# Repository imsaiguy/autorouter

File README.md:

# Visible Autorouter for KiCad

A multi-pass PCB autorouter that runs **inside KiCad** (toolbar button) or from the
command line, routes **all nets or just the ones you select**, and **shows its
thinking** while it works.

*Pass 1: every net takes its own shortest path and nets pile on top of each other
(yellow squares). Each later pass raises the price of contested copper. The
orange heat is the congestion "memory" the router has learned. Nets that have
alternatives move away; the curve on the right shows the overuse falling to
zero.*

## Get it

```bash
git clone https://github.com/imsaiguy/autorouter.git
```

or use **Code ▸ Download ZIP** on https://github.com/imsaiguy/autorouter. The
plugin is the `kicad_autorouter` folder; installation is described below.

### Install or update on Windows in one go (KiCad 10)

Save your work, then paste this into PowerShell. It closes KiCad, downloads the
latest version and installs it (the same block installs the first time and
updates afterwards):

```powershell
Get-Process python*, pythonw* -ErrorAction SilentlyContinue | Where-Object { $_.Path -like "*KiCad*" } | Stop-Process -Force
Get-Process kicad*, pcbnew*, eeschema* -ErrorAction SilentlyContinue | Stop-Process
Remove-Item -Recurse -Force "$env:TEMP\autorouter" -ErrorAction SilentlyContinue
Invoke-WebRequest https://github.com/imsaiguy/autorouter/archive/refs/heads/main.zip -OutFile "$env:TEMP\autorouter.zip"
Expand-Archive "$env:TEMP\autorouter.zip" "$env:TEMP\autorouter" -Force
"y" | & "C:\Program Files\KiCad\10.0\bin\python.exe" -u "$env:TEMP\autorouter\autorouter-main\kicad_autorouter\install_plugin.py"
```

Then start KiCad and open a board. The router's log should say
**"Search core: compiled (fast)"**.

## What it does

* **Three scopes:**
  * **Unrouted only** (the default): finishes just the missing connections,
    i.e. the ratsnest. **Existing tracks and vias are never moved or
    removed.** Partly routed nets get only their missing links, and new
    copper joins onto what's there.
  * **Selected:** the nets of the selected footprints, pads or tracks.
  * **All nets.**

  For *Selected* and *All* you can tick **Remove existing tracks** to re-route
  those nets from scratch. Otherwise existing copper is kept: connected pieces
  count as one terminal, and other nets' tracks are obstacles.
* **Global then detailed routing.** A coarse stage first plans each net's way
  through 2.7 mm regions, with PathFinder on region boundaries that have a
  capacity. The detailed grid search then stays inside that corridor, which
  widens if a net keeps conflicting and falls back to the full search if it is
  too tight. This is the same idea as tscircuit's capacity-mesh router. On the
  dense test board it is about 1.7× faster (60 s → 35 s) for about 2% more track
  length. Turn it off with `--no-global`.
* **Clean, 45° routing.** Every bend is 45°: no 90° corners, no hairpins.
  Straightening is always the last step (no option to turn it off): zig-zags,
  bumps, jogs and awkward joins become straight runs wherever the space is
  free, without cutting pours. The test suite checks that
  results have no corners sharper than 45° and no dead-end stubs.
* **Loose copper.** Track pieces that touch no pad (e.g. an unfinished trace)
  are never routed *to*, because that only grows dead-end stubs. They are
  reported, and **"Delete loose track pieces"** removes them in the same undo
  step.
* **Clear progress.** A progress bar with an estimated time remaining, a bar
  for the current pass, and live detail (pass, net *n* of *m*, conflicts left,
  elapsed time), with big **Route / Stop / Close** buttons. The estimate is
  learned from how fast conflicts are falling, and the bar never runs
  backwards.
* **Sees your existing work.** When it loads the design it shows existing
  tracks and vias (muted, so new routes stand out) and a summary such as
  *"8 routed · 1 partly routed · 2 unrouted"*. If a net can't be finished
  around fixed copper, it says which net and how to free it.
* **Multiple passes.** It uses the negotiated-congestion "PathFinder" algorithm
  with A* search per connection, which is the standard method for FPGA routing.
* **Visible thinking.** You can watch the A* wavefront, tentative tracks,
  overused cells, the learned congestion heatmap, and a convergence curve,
  either in the plugin's browser view, in a matplotlib window, or as a GIF.
* **Pours only count where they reach.** A pad counts as connected by a pour
  only if it lies inside that zone's outline. Every other pad of a pour net
  (GND, +5…) is routed into the pour, tree-style, so nearby pads share a track.
  The option **Route pour nets with tracks too** routes them like any other net.
* **Pours are part of the negotiation.** GND/power nets with a copper zone are
  left to the pour. SMD pads that are not on the pour layer get a short stub
  plus a via down to it. After each pass the router estimates the pour,
  detects pads or vias stranded on islands, and pushes the tracks that cut
  them off elsewhere.
* **Fast.** The A* search runs in a small compiled C library (`native/`,
  Linux x86-64 and Windows x64 shipped; elsewhere it falls back to the same
  search in Python, about 3–4× slower). Pass 1 runs on several CPU cores at once
  (one worker process per core, biggest nets first). A 120-net board with
  0.5 mm-pitch parts routes in about 30–60 s.
* **Net classes.** Each net keeps its class's track width and clearance (read
  from the `.kicad_pro`, or from KiCad itself in the plugins).
* **Ground planes done properly.** When a pour net (GND…) has a pour on
  another layer, every SMD pad gets its own short via down to it (or shares a
  neighbour's), instead of tracks wandering between pads. Signals have
  priority: a via that would block another net gives way. Zone outlines, zone
  priority and zone clearance are taken into account.
* **Solid planes.** On boards with more than two layers, an inner layer covered by
  a pour (GND or power plane) stays solid: other nets only pass through it with
  vias. Tick **Allow tracks on plane layers** (`--tracks-on-planes`) to route
  signals there too. Ground and power have priority: they are never dropped to
  make room for signals.
* **Fine-pitch escapes.** Pads too close together for the grid get a short
  off-grid stub (down to the minimum track width) to the nearest usable grid
  point.
* **A second chance for dropped nets.** If the negotiation has to drop a few
  nets, a rescue pass tries each again on the finished board, and then
  re-routes it together with the nets it was fighting, in every order (up to
  3 s per net).
* **Says why.** Nets that could not be finished are listed with the reason:
  walled in (by which pads or tracks), or "no room left - it was fighting X
  and Y for the same space".
* **Stop when you like.** Stop offers two choices: **Discard** (nothing is
  written) or **Keep**, which straightens what was routed, exactly like a
  finished run.
* **Straighten a board from the command line.** `--straighten-only` runs the
  same clean-up on the copper already in a `.kicad_pcb` file, without routing
  anything (off-grid pieces such as hand-drawn tracks stay as they are).
* **Checked with KiCad's own DRC.** On the demo board the result has
  **0 clearance, short, edge or hole violations and 0 unconnected items**.
  The test suite runs that check.

## How it thinks

The board becomes a grid whose pitch is `track width + clearance`. Tracks run
along cell centres, so *one cell = one net* **is** the clearance rule. Two extra
rules keep that true everywhere else:

* a 45° step must clear fixed copper at its middle point (checked on a second
  map, offset half a cell), and it books the two side cells it squeezes past:
  another net's track there is a conflict, another 45° step's side cell is
  not (two parallel diagonals one cell apart are 1.41 pitch apart);
* a via claims every cell within `via radius + clearance + track width/2`, on
  every layer;
* a net in a wider net class (say a 24 mil "power" class) claims a square of
  `r` cells round its centre-line, the smallest `r` with
  `(r + 1) · pitch ≥ W/2 + w/2 + C` (W, C: the class's width and clearance;
  w: the Default width). It keeps that width all the way; only in the last
  cell or two before one of its own pads, where the neighbouring pads leave
  no room, may it narrow to the Default width.
* a new branch may leave or join an earlier track of its net only at 90° or
  wider (a T, never a sharp Y), and the clean-up pass keeps it that way.

Pads, existing tracks and the board edge give each cell an owner: free, "only
net *n*" (inside *n*'s clearance halo), or blocked.

Each pass then does this:

```
global plan: PathFinder on a coarse grid of regions -> one corridor per net
for each net that is in conflict:              (all nets in pass 1)
    rip up its old route
    grow a tree from one pad; repeatedly A* to the nearest unconnected pad
        cost of a cell = (1 + history) × (1 + present_factor × other_nets_in_cell)
        × direction factor (F.Cu prefers horizontal, B.Cu vertical) + bend + via costs
        the search state includes the arrival direction, so only 0° / 45° turns are allowed

after the pass:
    overused cell  = used by 2+ nets
    history       += history_factor × overuse        (remembers chronic hot spots)
    present_factor ×= 1.6                             (contention gets pricier every pass)
    pour check: a pour pad/via cut off onto an island → its walls get pricier too
stop when nothing is overused
then: straighten every route (zig-zag -> straight / straight+45°) using only free cells
```

This works like a market. Copper is a shared resource and its price rises with
demand. Nets with cheap alternatives leave the contested cells. Nets with no
alternative stay, because everyone else has learned to avoid that spot. The
present-cost factor only ever rises, so it also resembles annealing: the
system gradually "freezes" into a legal solution. If it hasn't converged after
`max_passes`, the most-conflicted nets are dropped and reported, so the output
is always DRC-legal.

## Install in KiCad

**KiCad 10 only.** The plugin uses KiCad's IPC API (the classic `pcbnew`
Python plugin interface is being retired by KiCad, and the old classic version
of this plugin has been removed; the installer deletes it if it finds it). Only
a tiny launcher button still uses the classic interface (see *Toolbar button*).

### KiCad 10

**Easiest: use the installer.** Close KiCad, then run it with the Python that
ships with KiCad:

```powershell
# Windows (PowerShell or cmd), from the folder you cloned / unzipped
& "C:\Program Files\KiCad\10.0\bin\python.exe" kicad_autorouter\install_plugin.py
```
```bash
# macOS / Linux
python3 kicad_autorouter/install_plugin.py
```

It does four things:

* copies the plugin to the folder KiCad 10 really loads from. It asks Windows
  for your Documents folder, so OneDrive-redirected Documents work.
* offers to remove stray copies from earlier attempts.
* turns on **Enable KiCad API** (it's off by default).
* checks the result.

Then start KiCad, open a board, and give it a minute the first time.

**Or by hand:**

1. **Turn the KiCad API on.** It is **off by default**. Go to
   **Preferences ▸ Preferences ▸ Plugins** and tick the option that enables
   the KiCad API.
2. **Copy the `kicad_autorouter` folder** (the whole folder, not its contents)
   into KiCad's **`plugins`** folder. Create the folder if it doesn't exist.

   | OS | folder |
   |---|---|
   | Windows | `Documents\KiCad\10.0\plugins\` |
   | macOS | `~/Documents/KiCad/10.0/plugins/` |
   | Linux | `~/.local/share/kicad/10.0/plugins/` |

   You should end up with `.../10.0/plugins/kicad_autorouter/plugin.json`.
   **Note: this is `plugins`, not `scripting/plugins`.** Subfolders are fine.
3. **Restart KiCad.** The first time, KiCad builds a small Python environment
   for the plugin and installs `kicad-python` from `requirements.txt`. That
   needs internet access once and can take a minute before the button becomes
   active.
4. Open a board. The **Visible Autorouter** button (two crossing traces) is on
   the PCB editor's toolbar.

Click it and your web browser opens the router's window. It shows your board
with its existing tracks and a routed / partly routed / unrouted summary.
Choose **Unrouted only** (the default), **Selected**, or **All nets**, check
the rules (they come from the Default net class; nets in other net classes
keep their own width and clearance), and press **Route**. The
board view shows the router thinking, and the chart shows conflicts dropping
pass by pass.

When it finishes, the tracks and vias go onto your board as **one undo step**
(Edit ▸ Undo removes them all), and zones are refilled. Press **Close** when
you're done.

**Toolbar button.** KiCad 10 shows a plugin's own button only after some checks
it repeats at every start, and on some PCs it never shows it. So the installer
also adds a small classic-style button (`scripting/plugins/visible_autorouter_launcher`)
that does nothing but start the plugin. You may see one button or two; both
open the same router.

**No toolbar button?** The plugin can always be started by hand while KiCad
has a board open. Double-click `run_autorouter.bat` in the plugin folder
(Windows), or run `kicad_autorouter/run_autorouter.sh` (macOS/Linux). It does
exactly what the button does.

### Button not showing?

Run the checker. It needs only the standard library and works with any
Python 3:

```bash
python kicad_autorouter/check_install.py
```

It checks the four conditions KiCad 10 needs before it shows an IPC plugin
button (taken from KiCad 10.0's source) and prints what to fix:

1. **The plugin folder.** `plugin.json` must be under `.../10.0/plugins/`;
   KiCad searches subfolders, so ZIP nesting is fine. (`scripting/plugins` is
   the old location for classic plugins, not this one.)
2. **The KiCad API is enabled.** It is off by default: Preferences ▸
   Preferences ▸ Plugins.
3. **A usable Python interpreter.** Windows and macOS use KiCad's bundled
   Python. Linux uses `python3` and needs the `venv` module
   (`sudo apt install python3-venv` on Debian/Ubuntu). On **Linux with
   Python 3.14**, `kicad-python`'s dependencies have no prebuilt wheels yet,
   so point KiCad at Python 3.11–3.13.
4. **The plugin environment is built.** At startup KiCad creates a virtual
   environment and pip-installs `kicad-python` (needs internet once). **The
   button only appears after this succeeds**, so after changing anything,
   **restart KiCad and wait a minute**. *Refresh Plugins* does not rebuild
   it.

**Plugin works but there's no button, and no Scripting Console (Python logo)
icon either?** KiCad 10 lets you customise toolbars and saves the layout in
`toolbars/pcbnew-toolbars.json` in your KiCad settings folder. If that saved
top toolbar lacks the plugin area (`control.IPCPlugin`), KiCad never shows
plugin buttons. The checker detects this, and `install_plugin.py` adds the
area back (with a backup).

## Command line (no KiCad GUI needed)

```bash
python -m kicad_autorouter board.kicad_pcb -o routed.kicad_pcb
python -m kicad_autorouter board.kicad_pcb --nets SDA,SCL           # only these nets
python -m kicad_autorouter board.kicad_pcb --gif thinking.gif       # record the thinking
python -m kicad_autorouter board.kicad_pcb --live                   # watch in a window
```

The CLI reads the `.kicad_pro` next to the board for the net classes (Default
plus any other class, with its net assignments and wildcard patterns).
Options include `--track-width --clearance --via-diameter --via-drill --grid
--layers F.Cu,B.Cu --passes --via-cost --include-zone-nets`. The core is pure
Python with no dependencies. Only `--gif/--png/--live` need matplotlib (and
Pillow for GIFs).

As a library:

```python
from kicad_autorouter import route, RouteSettings
from kicad_autorouter.kicad_pcb import PcbFile

pcb = PcbFile("board.kicad_pcb")
result = route(pcb.board(), pcb.settings_from_project(), nets=["SDA", "SCL"],
               callback=lambda ev, data: print(ev, data.get("pass")))
pcb.add_routes(result, pcb.settings_from_project()); pcb.save("routed.kicad_pcb")
```

## Layout

| file | what |
|---|---|
| `kicad_autorouter/model.py` | board model (pads, tracks, vias, outline) in mm, plus `RouteSettings` |
| `kicad_autorouter/problem.py` | board → grid, clearance halos, terminal clustering, pour anchors |
| `kicad_autorouter/global_route.py` | coarse global routing: region capacities, PathFinder on region boundaries, corridors |
| `kicad_autorouter/router.py` | A*, PathFinder passes, pour check, events, geometry output |
| `kicad_autorouter/viz.py` | matplotlib live view / GIF / PNG |
| `kicad_autorouter/kicad_pcb.py` | `.kicad_pcb` reader and writer (KiCad 6–9 S-expression format) |
| `kicad_autorouter/plugin.json`, `ipc_action.py`, `requirements.txt` | KiCad 10 IPC plugin manifest and entry point |
| `kicad_autorouter/install_plugin.py` | one-step installer for KiCad 10 (copy, enable API, remove old copies, check) |
| `kicad_autorouter/check_install.py` | "why no button?" checker for KiCad 10 installs |
| `kicad_autorouter/ipc_plugin.py`, `ipc_ui.html` | KiCad 10 adapter (kicad-python), browser thinking view, single-commit writeback |
| `kicad_autorouter/native/` | the compiled A* search (C source, Linux and Windows builds, build script) |
| `kicad_autorouter/parallel.py` | pass 1 on several CPU cores |
| `examples/make_test_board.py` | builds the demo board with KiCad's own `pcbnew` API |
| `examples/drc_check.py` | fills zones and runs KiCad's DRC on a board |
| `tests/` | exact-geometry clearance and connectivity checks, KiCad DRC test, and IPC-adapter tests on real `kipy` objects |

```bash
python -m pytest tests        # the DRC test runs when pcbnew is importable
```

## Status and honest limitations

What's been tested:

* **KiCad 10 on Windows:** used daily on real boards (Arduino UNO R4 and Leonardo, a WSPR
  transmitter, a 99-net attenuator controller). Results are checked with
  KiCad 10's DRC (`kicad-cli pcb drc --refill-zones`). The compiled core runs
  on Windows x64.
* **KiCad 10 adapter tests:** the manifest validates against KiCad 10.0's
  plugin schema, and tests drive the adapter with real `kipy` objects.

* Net classes: track width and clearance are honoured per net. Vias use the
  Default class's via size for every net. Custom DRC rules (`.kicad_dru`) are
  not read.
* Grid router. Very fine-pitch parts (≤ 0.5 mm) may be hard to escape; try a
  smaller `--grid`. Off-grid pads are reached with a short stub to the pad
  centre.
* Through vias only. No differential pairs, no length tuning. No via-in-pad.
* Pours are estimated on the grid. Occasionally a pad the router counts as
  joined by a pour is not reached when KiCad fills the zone: run KiCad's DRC
  after routing a board with pours.
* macOS has no compiled core yet (it uses the slower Python search).
* Very crowded spots (e.g. a 0.5 mm-pitch regulator surrounded by its
  resistors on a 2-layer board) can leave a few short nets to finish by hand;
  they are listed with the nets they were fighting.
* **Rule areas / keepouts are not read yet.** Check DRC if your board uses them.
* Odd pad shapes: custom pads use their exact outline (KiCad's own polygon in
  both plugins; rebuilt from the pad's primitives by the command line). Trapezoid
  and chamfered pads are exact in the plugins and slightly enlarged on the command
  line. Anything approximated is approximated outward, never inward; a test
  checks this against KiCad's own pad hit-test on rotated and flipped footprints.
* The pour estimate is approximate. Refill the zones and run DRC afterwards
  (the plugin refills for you).
* Speed: the path search (the inner loop, ~80% of the time) is compiled C
  (`kicad_autorouter/native/astar.c`, loaded with ctypes, so one file per OS works
  with any Python): Linux x86-64 and Windows x64 are shipped; elsewhere the same
  search runs in Python, with identical routes, about 5-10x slower. The log says
  which one runs ("Search core: compiled"). Arduino Leonardo (52 nets, 2 layers):
  26 s; 34 random nets on 100 x 70 mm: under 3 s. `native/build.sh` rebuilds it.
* Multi-core: only the first pass (all nets routed "as if alone", usually the
  longest pass) uses all CPU cores, as separate worker processes; on a board of
  ~160 mostly local nets that made the whole run 1.4× faster on 3 cores. The
  later passes negotiate one net at a time, which is inherently sequential: run
  in parallel, nets that cannot see each other kept grabbing the same cells.
  Boards with fewer than 20 nets stay on one core (starting workers costs ~1 s).
  `--workers N` on the command line overrides the automatic choice.

## Ideas for next steps

* Live preview on the KiCad 10 canvas itself, in addition to the browser view.
* Rule areas, per-class via sizes and custom DRC rules.
* A C/Rust inner loop for the A* search.
* A post-route "push-and-shove" cleanup pass to straighten tracks and remove
  extra vias.

## License

MIT - see [LICENSE](LICENSE). Free to use, change and share; keep the copyright notice.

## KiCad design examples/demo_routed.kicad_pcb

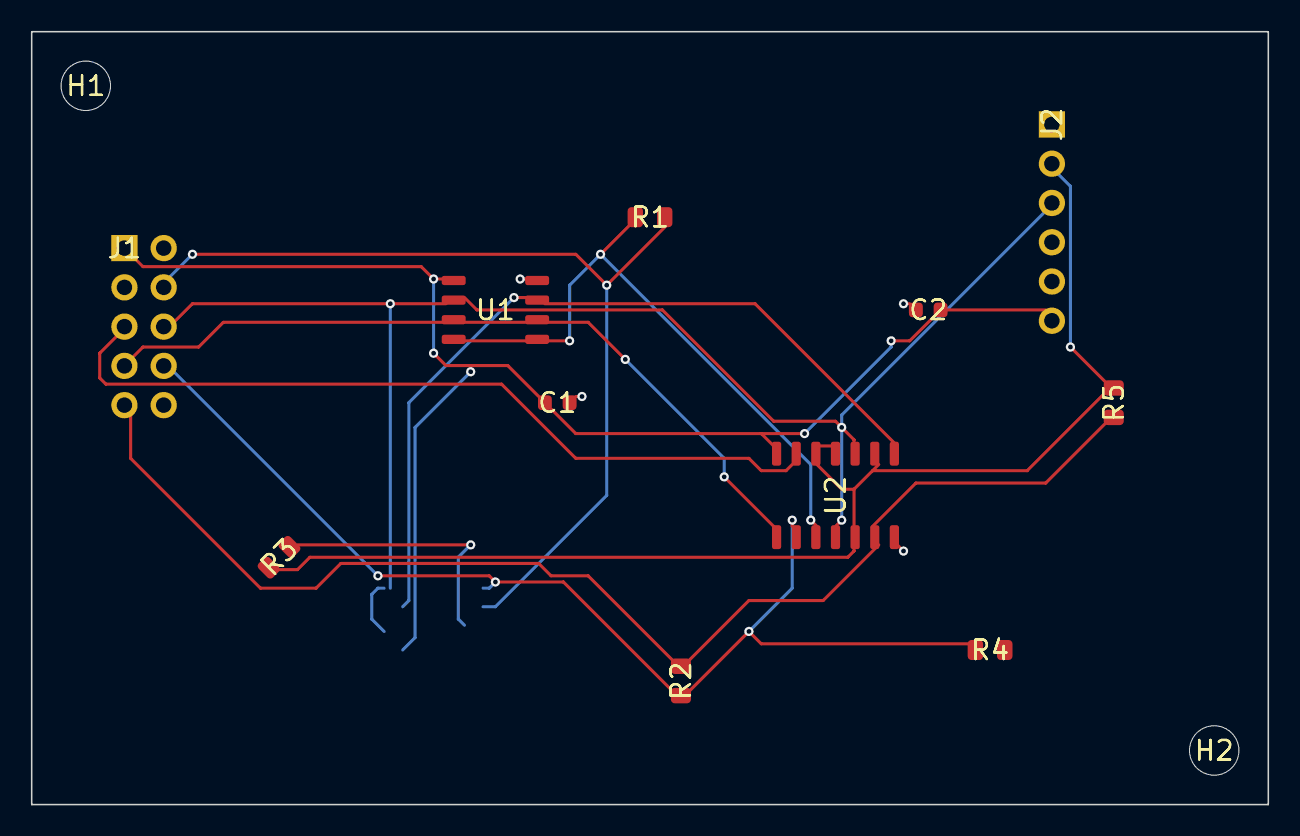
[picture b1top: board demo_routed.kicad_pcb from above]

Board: 2 copper layers, 80.0 x 50.0 mm, 14 parts (1 on the bottom side), 12 nets.

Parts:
C1: C1
C2: C2
H1: H1
H2: H2
J1: J1
J2: J2
R1: R1
R2: R2
R3: R3
R4: R4
R5: R5
U1: U1
U2: U2
U3: U3

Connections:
+3V3: C1.1, C2.1, J1.1, J2.6, U1.1, U2.14, U3.1
CLK: J1.8, R2.1, R4.1, U2.2, U3.5
D1: J1.6, J2.3, U1.2, U2.4, U2.10, U3.2, U3.4
D2: J1.7, U1.3, U1.6, U2.1
D3: J1.9, R2.2, R5.1, U2.6
D4: J1.4, R1.2, U3.6
D7: U1.7, U2.8, U3.3
D9: R3.2, U3.7
D12: J1.5, U2.13
D13: R1.1, U1.4, U1.5, U2.3
EN: J2.2, R3.1, R5.2, U2.5, U2.9, U2.11, U2.12
GND: C1.2, C2.2, J1.2, J2.1, U1.8, U2.7, U3.8
